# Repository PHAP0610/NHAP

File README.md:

# STM32F103

## Hardware BOARD V0.1

All file include and source in this: https://github.com/nguyentrungthao/STM32/tree/dev

### Module 7 segment with two ic 74595
1. Pin configuration.

<!-- cách ra 1 dòng để git hiểu là xuống hàng -->
<!-- :--- là căn trái :---: là căn giữa ---: là căn phải trong cột -->
| STM32 | 74595  | 
| :---: | :---: | 
| PA4 | SER |
| PA5 | OE |
| PA6 | RCLK |
| PA7 | SRCLK |

2. Code 

high 8-bit to select a 7-segment digit 
low 8-bit is code-7-segment 
code7segment is used in this board sequence:
<!--  có nhiều fotmat khác như c, cpp, js, html,...... -->
```c
/* this code only use for this version board */
const char code7seg[] = {0xD7, 0x14, 0xCD, 0x5D, 0x1E, 0x5B, 0xDB, 0x15, 0xDF, 0x5F};
```
### Module rotary encoder 
1. Pin configuration 

| STM32 | Rotary Encoder | description | 
| :---: | :---: | :--- |
| PA8 | channel A | pull up |
| PA9 | channel B | pull up |
| PA10 | buttuon | pull up |

2. Code

PA8 - PA9 is encoder mode of timer1 
```c
/* Enable TIM1 encoder mode */
/* USER CODE BEGIN 2 */
HAL_TIM_Encoder_Start_IT(&htim1, TIM_CHANNEL_ALL);
/* USER CODE END 2 */

/* Get encoder value */
encoderValue = __HAL_TIM_GetCounter(&htim1);
```

### AC voltage control
1. Pin configuration 

| STM32 | Module | description |
| :---: | :---: | :--- |
| PB0 | AC Detec| pull up |
| PB1 | Triac |  |

2. code 

PB0 should be an EXT pin 
``` c
/* proccess when interrupt */
void HAL_GPIO_EXTI_Callback(uint16_t GPIO_Pin){
	if(GPIO_Pin == ACDET_Pin){
		SETFLAG(FLAG_ACDET_TRIGGER, flag);
        // control angle to set triac base on time which is calculated by PID
		__HAL_TIM_SET_COUNTER(&htim4, (uint16_t)(triac.giaTriDieuKhien * 1000));
//		__HAL_TIM_SET_COUNTER(&htim4, 9000);
	}
}
```

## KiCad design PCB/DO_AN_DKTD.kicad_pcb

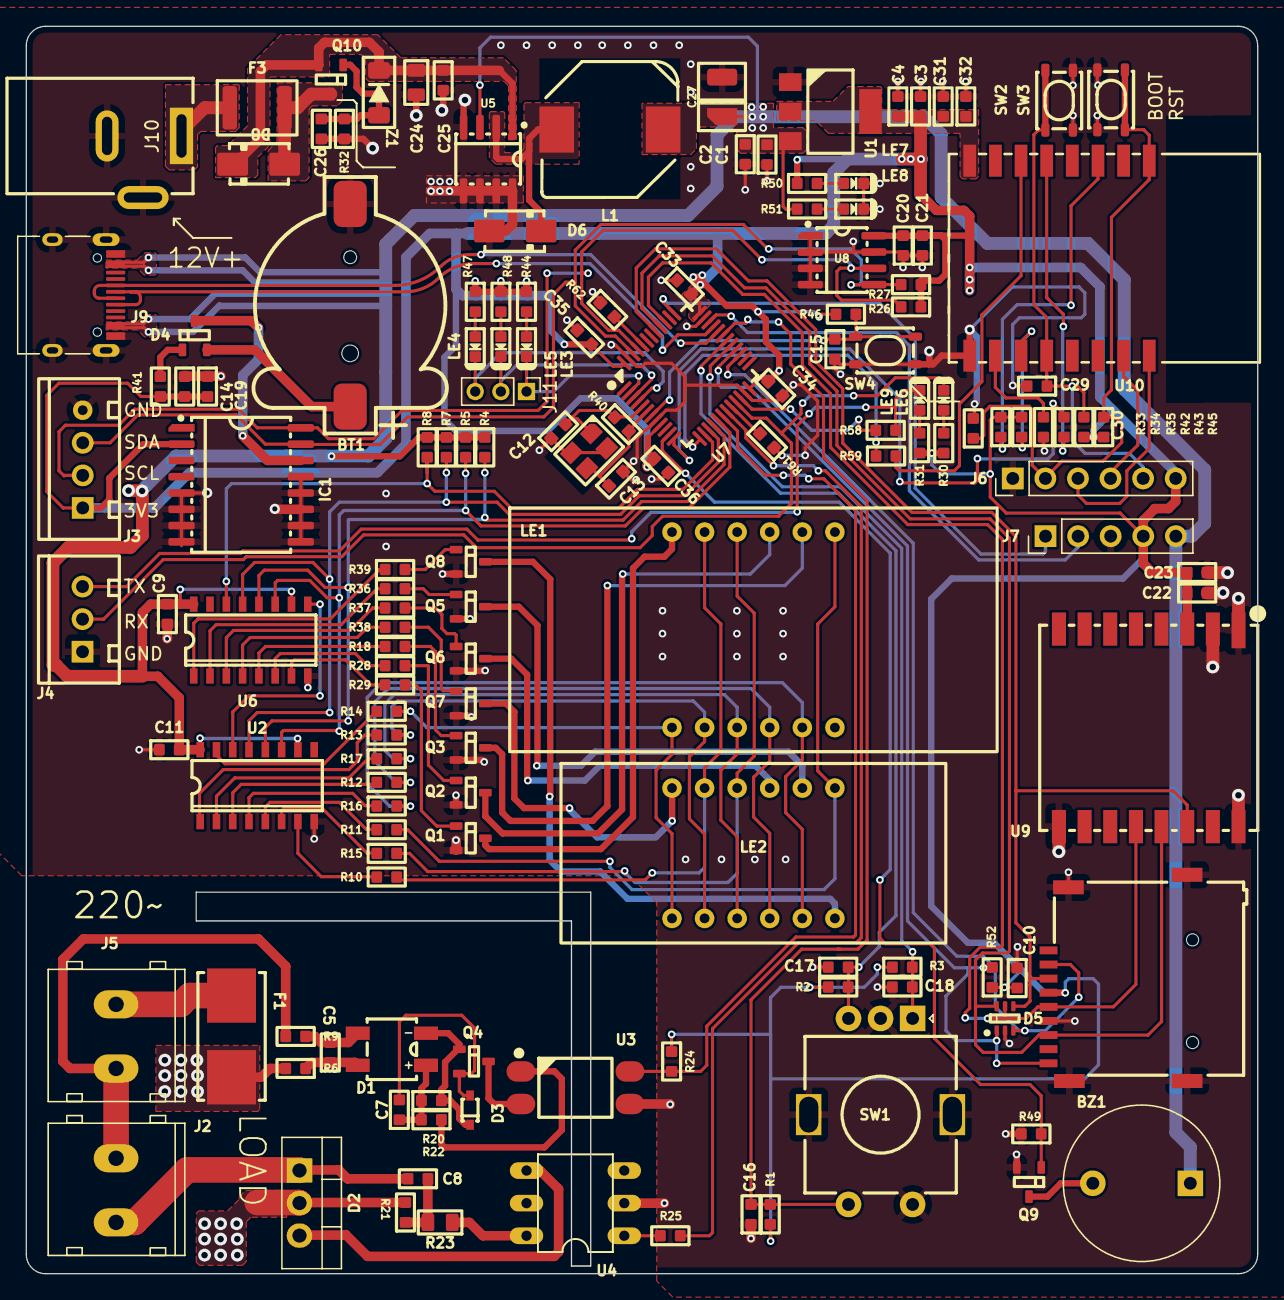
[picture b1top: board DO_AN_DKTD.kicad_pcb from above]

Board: 2 copper layers, 96.0 x 97.2 mm, 147 parts (0 on the bottom side), 115 nets.

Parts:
BT1: CR1220; BatteryHolder_CR1220
BZ1: Buzzer; Buzzer_12x9.5RM7.6
C1, C3, C15, C16, C17, C18, C22, C25, C29, C30, C31: 1uF; C_0603
C2, C4, C9, C10, C11, C19, C21, C23, C26, C32, C33, C34, C35, C36: 100nF; C_0603
C5: 10nF; C_0603
C7, C14, C20: 10uF; C_0603
C8: 50nF; C_0603
C12, C13: 22pF; C_0603
C24: 10uF; C_0805
C27: 10uF; CP_EIA-3528-15_AVX-H
D1: MB10F; DiodeBridge_MB10F-13AQ
D2: TRIAC; TO-220-3_Vertical
D3: 1N4148; D_SOD323
D4: BAT54C; SOT23-3
D5: SMF05C; TSSOP-6
D6, D8: SS54; D_SMA
F1: Fuse; Fuseholder_Littelfuse_Nano2_154x
F3: Fuse; Fuse_1812_4532Metric
IC1: RTC_DS3231M; SOIC-16W_7.5x10.3mm_P1.27mm
J2, J5: Conn_01x02; KF128-5.0-2P
J3: Conn_01x04; Conn_XH-P2.54mm-4P
J4: Conn_01x03; Conn_XH-P2.54mm-3P
J6: PinHeader_1x06_P2.54mm_Vertical
J7: Conn_01x05_Male; PinHeader_1x05_P2.54mm_Vertical
J9: USB_C_Receptacle; USB_C_Receptacle_XKB_U262-16XN-4BVC11
J10: Jack-DC; BarrelJack_Wuerth_6941xx301002
J11: Conn_01x03_Pin; PinHeader_1x03_P2.00mm_Vertical
J12: Micro_SD_Card_Det1; Socket_MicroSD-9P
L1: 68uH 2A; L_10.4x10.4_H4.8
LE1: 5631AS; 7Segment_4led_CC_38x19
LE2: 5631AS; 7Segment_4led_Cathode_30x14mm
LE3, LE4, LE5, LE6, LE7, LE8, LE9: Led; LED_0603
Q1, Q2, Q3, Q4, Q5, Q6, Q7, Q8: NPN; SOT23-3
Q9: N_Mosfet; SOT23-3
Q10: P_Mosfet; SOT23-3
R1, R2, R3, R4, R5, R7, R8, R26, R27, R52: 4k7; R_0603
R6, R9: 180k; R_0603
R10, R11, R12, R13, R14, R15, R16, R17, R22, R24, R30, R31, R41, R44, R47, R48, R50, R51: 1k; R_0603
R18, R28, R29, R36, R37, R38, R39: 2k; R_0603
R20: 22k; R_0603
R21: 470; R_0603
R23: 360; R_0805
R25: 360; R_0603
R32: 12k; R_0603
R33, R34, R35, R43, R45, R46: 10k; R_0603
R40, R49: 1M; R_0603
R42: 100; R_0603
R58, R59: 100R; R_0603
R61, R62: 10K; R_0603
SW1: RotaryEncoder_Switch; RotaryEncoder_Alps_EC11E-Switch_Vertical_H20mm
SW2, SW3, SW4: SW_Push; SW_SPST_PTS810
U1: AMS1117; SOT233
U2, U6: 74HC595; SOIC-16W_3.92x10.2mm
U3: PC817; OPTO_SOT254P975X400-4N
U4: MOC3020M; DIL06-E
U5: XL1509; SOIC-8_3.9x4.9mm_P1.27mm
U7: STM32F103C8Tx; LQFP-48_7x7mm_P0.5mm
U8: 24C32N; SOIC-8_3.9x4.9mm_P1.27mm
U9: Ai-Thinker-Ra-02; MODULE_RA-02_LORA
U10: ESP-07; ESP8266-07__ESP32-C3-12F
Y1: Crystal_GND24_Small; Crystal-SMD-4P-3.2x2.6mm-3225
Z1: D_Zener; D_MiniMELF

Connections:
+3V3: C3.2, C4.1, C10.2, C14.2, C19.2, C20.2, C21.2, C22.1, C23.1, C31.1, C32.1, C33.2, C34.2, C35.2, C36.2, IC1.2 (VCC), J3.1, J6.6, J7.4, J12.4 (VDD), R1.1, R2.1, R3.1, R24.1, R26.1, R27.1, R30.1, R31.1, R33.2, R34.2, R41.1, R43.1, R44.1, R45.1, R46.1, R47.1, R48.1, R50.1, R52.1, U1.2 (VO), U7.9 (VDDA), U7.24 (VDD), U7.36 (VDD), U7.48 (VDD), U8.8 (VCC), U9.3 (VDD), U10.8 (VCC)
+5V: BZ1.1 (-), C1.2, C2.1, C9.2, C11.2, C27.1, J7.5, J9.A4 (VBUS), J9.A9 (VBUS), J9.B4 (VBUS), J9.B9 (VBUS), L1.2, R4.1, R5.1, R7.1, R8.1, R51.1, U1.3 (VI), U2.10 (~SRCLR), U2.16 (VCC), U5.3 (FB), U6.10 (~SRCLR), U6.16 (VCC)
/74HC595_HEADER_OUTPUT/74HC595.OE: R7.2, U2.13 (~OE), U6.13 (~OE), U7.15 (PA5)
/74HC595_HEADER_OUTPUT/74HC595.RCLK: R4.2, U2.12 (RCLK), U6.12 (RCLK), U7.16 (PA6)
/74HC595_HEADER_OUTPUT/74HC595.SER: R8.2, U6.14 (SER), U7.14 (PA4)
/74HC595_HEADER_OUTPUT/74HC595.SRCLK: R5.2, U2.11 (SRCLK), U6.11 (SRCLK), U7.17 (PA7)
/74HC595_HEADER_OUTPUT/LE1: R29.1, U6.7 (QH)
/74HC595_HEADER_OUTPUT/LE2: R28.1, U6.6 (QG)
/74HC595_HEADER_OUTPUT/LE3: R18.1, U6.5 (QF)
/74HC595_HEADER_OUTPUT/LE4: R38.1, U6.4 (QE)
/74HC595_HEADER_OUTPUT/LE5: R37.1, U6.3 (QD)
/74HC595_HEADER_OUTPUT/LE6: R36.1, U6.2 (QC)
/74HC595_HEADER_OUTPUT/LE7: R39.1, U6.1 (QB)
/74HC595_HEADER_OUTPUT/LOG_RX: J4.2, LE6.2, U7.21 (PB10)
/74HC595_HEADER_OUTPUT/LOG_TX: J4.3, LE9.2, R58.1
/74HC595_HEADER_OUTPUT/SHT31.SCL: IC1.16 (SCL), J3.2, R26.2, U7.45 (PB8), U8.6 (SCL)
/74HC595_HEADER_OUTPUT/SHT31.SDA: IC1.15 (SDA), J3.3, R27.2, U7.46 (PB9), U8.5 (SDA)
/74HC595_HEADER_OUTPUT/a: LE1.11 (a), LE2.11 (a), R10.2
/74HC595_HEADER_OUTPUT/b: LE1.7 (b), LE2.7 (b), R11.2
/74HC595_HEADER_OUTPUT/c: LE1.4 (c), LE2.4 (c), R12.2
/74HC595_HEADER_OUTPUT/d: LE1.2 (d), LE2.2 (d), R13.2
/74HC595_HEADER_OUTPUT/dot: LE1.3 (DPX), LE2.3 (DPX), R17.2
/74HC595_HEADER_OUTPUT/e: LE1.1 (e), LE2.1 (e), R14.2
/74HC595_HEADER_OUTPUT/f: LE1.10 (f), LE2.10 (f), R15.2
/74HC595_HEADER_OUTPUT/g: LE1.5 (g), LE2.5 (g), R16.2
/BUZZER/Buzzer: Q9.1 (G), R49.1, U7.11 (PA1)
/ESP/BOOT: C29.1, J6.5, R43.2, SW3.2, U10.18 (GPIO0)
/ESP/RST: C30.1, J6.2, R45.2, SW2.2, U10.1 (~RST)
/ESP/RX: J6.4, U10.21 (GPIO3/RXD)
/ESP/RX_ESP32: R42.2, U7.12 (PA2)
/ESP/TX: J6.3, U10.22 (GPIO1/TXD)
/ESP/TX_ESP32: R59.2, U10.6 (GPIO12)
/LORA/LORA.MISO: D5.6, J12.7 (DAT0), U7.40 (PB4), U9.13 (MISO)
/LORA/LORA.MOSI: D5.4, J12.3 (CMD), U7.41 (PB5), U9.14 (MOSI)
/LORA/LORA.SCK: D5.5, J12.5 (CLK), U7.39 (PB3), U9.12 (SCK)
/MICRO_SD/SD.CS: D5.3, J12.2 (DAT3/CD), U7.27 (PB14)
/MICRO_SD/SD.DET: D5.1, J12.9 (DET), R52.2, U7.28 (PB15)
/POWER/B: D8.1, F3.2, Q10.3 (D)
/POWER/VIN: F3.1, J10.1
/POWER/VOUT: D6.2, L1.1, U5.2 (OUTPUT)
/RTC_DS3231/Vbat: BT1.1 (+), D4.2
/STM32/ACDET: R24.2, U3.4, U7.18 (PB0)
/STM32/Led_test1: J11.1, LE3.2, U7.2 (PC13)
/STM32/Led_test2: J11.2, LE5.2, U7.3 (PC14)
/STM32/Led_test3: J11.3, LE4.2, U7.4 (PC15)
/STM32/PD0: C12.2, R40.1, U7.5 (PD0), Y1.1
/STM32/PD1: C13.1, R40.2, U7.6 (PD1), Y1.3
/STM32/RST: C15.1, R46.2, SW4.2, U7.7 (NRST)
/STM32/ST.D+: J9.A6 (D+), J9.B6 (D+), U7.33 (PA12)
/STM32/ST.D-: J9.A7 (D-), J9.B7 (D-), U7.32 (PA11)
/STM32/ST.EnC_A: C18.2, R3.2, SW1.A, U7.29 (PA8)
/STM32/ST.EnC_B: C17.2, R2.2, SW1.B, U7.30 (PA9)
/STM32/ST.EnC_BT: C16.2, R1.2, SW1.S1, U7.31 (PA10)
/STM32/SWCLK: J7.1, U7.37 (PA14)
/STM32/SWDIO: J7.2, U7.34 (PA13)
/STM32/TRIAC: R25.1, U7.19 (PB1)
/TRIAC_ACDET/L: F1.2, J5.1
/TRIAC_ACDET/L_after: D2.2 (A2), F1.1, R6.2, R21.2
/TRIAC_ACDET/Load: C8.2, D2.1 (A1), J2.2
/TRIAC_ACDET/N: J2.1, J5.2, R9.2
GND: BT1.2 (-), C1.1, C2.2, C3.1, C4.2, C9.1, C10.1, C11.1, C12.1, C13.2, C14.1, C15.2, C16.1, C17.1, C18.1, C19.1, C20.1, C21.1, C22.2, C23.2, C24.2, C25.2, C26.2, C27.2, C29.2, C30.2, C31.2, C32.2, C33.1, C34.1, C35.1, C36.1, D5.2, D6.1, IC1.5 (GND), IC1.6 (GND), IC1.7 (GND), IC1.8 (GND), IC1.9 (GND), IC1.10 (GND), IC1.11 (GND), IC1.12 (GND), IC1.13 (GND), J3.4, J4.1, J6.1, J7.3, J9.A1 (GND), J9.A12 (GND), J9.B1 (GND), J9.B12 (GND), J9.S1 (SHIELD), J10.2, J12.6 (VSS), J12.10 (SHIELD), LE7.2, LE8.2, Q1.2 (E), Q2.2 (E), Q3.2 (E), Q5.2 (E), Q6.2 (E), Q7.2 (E), Q8.2 (E), Q9.2 (S), R32.2, R35.1, R49.2, R61.1, R62.1, SW1.C, SW1.MP (Shield), SW1.S2, SW2.1, SW3.1, SW4.1, U1.1 (GND), U2.8 (GND), U3.3, U4.2, U5.4 (ON/OFF), U5.5 (GND), U5.6 (GND), U5.7 (GND), U5.8 (GND), U6.8 (GND), U7.8 (VSSA), U7.23 (VSS), U7.35 (VSS), U7.47 (VSS), U8.1 (A0), U8.2 (A1), U8.3 (A2), U8.4 (GND), U8.7 (WP), U9.1 (GND), U9.2 (GND), U9.9 (GND), U9.16 (GND), U10.15 (GND), Y1.2, Y1.4
unnamed: D4.3, IC1.14 (VBAT)
unnamed: BZ1.2 (+), Q9.3 (D)
unnamed: C5.1, D1.4, R6.1
unnamed: C5.2, D1.2, R9.1
unnamed: C8.1, R21.1, R23.2
unnamed: C7.1, D1.1 (+), R20.1, R22.2
unnamed: D1.3 (-), D3.2, Q4.1 (B), R20.2
unnamed: D2.3 (G), U4.4
unnamed: D4.1, R41.2
unnamed: LE1.12 (CC1), Q1.3 (C)
unnamed: LE1.9 (CC2), Q2.3 (C)
unnamed: LE1.8 (CC3), Q3.3 (C)
unnamed: LE2.12 (CC1), Q7.3 (C)
unnamed: LE2.9 (CC2), Q6.3 (C)
unnamed: LE2.8 (CC3), Q5.3 (C)
unnamed: LE2.6 (CC4), Q8.3 (C)
unnamed: LE3.1, R44.2
unnamed: LE4.1, R47.2
unnamed: LE5.1, R48.2
unnamed: LE6.1, R30.2
unnamed: LE7.1, R50.2
unnamed: LE8.1, R51.2
unnamed: LE9.1, R31.2
unnamed: Q1.1 (B), R29.2
unnamed: Q2.1 (B), R28.2
unnamed: Q3.1 (B), R18.2
unnamed: Q4.3 (C), U3.2
unnamed: C7.2, D3.1, Q4.2 (E)
unnamed: Q5.1 (B), R36.2
unnamed: Q6.1 (B), R37.2
unnamed: Q7.1 (B), R38.2
unnamed: Q8.1 (B), R39.2
unnamed: C26.1, Q10.1 (G), R32.1, Z1.1
unnamed: R22.1, U3.1
unnamed: R23.1, U4.6
unnamed: R25.2, U4.1
unnamed: R14.1, U2.15 (QA)
unnamed: R13.1, U2.1 (QB)
unnamed: R17.1, U2.2 (QC)
unnamed: R12.1, U2.3 (QD)
unnamed: R16.1, U2.4 (QE)
unnamed: R11.1, U2.5 (QF)
unnamed: R15.1, U2.6 (QG)
unnamed: R10.1, U2.7 (QH)
unnamed: U2.14 (SER), U6.9 (QH')
unnamed: R62.2, U7.44 (BOOT0)
unnamed: R59.1, U7.13 (PA3)
unnamed: R61.2, U7.20 (PB2)
unnamed: R58.2, U7.22 (PB11)
unnamed: R33.1, U10.3 (EN)
unnamed: R34.1, U10.17 (GPIO2)
unnamed: R42.1, U10.5 (GPIO14)
unnamed: R35.2, U10.16 (GPIO15)
VDC: C24.1, C25.1, D8.2, Q10.2 (S), U5.1 (VIN), Z1.2

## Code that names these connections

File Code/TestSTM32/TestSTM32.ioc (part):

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Mcu.Name=STM32F103C(8-B)Tx
Mcu.Package=LQFP48
Mcu.UserName=STM32F103C8Tx
PA1.GPIOParameters=GPIO_Label
PA1.GPIO_Label=BUZZER
PA1.Signal=GPIO_Output
PA10.GPIOParameters=GPIO_PuPd,GPIO_Label,GPIO_ModeDefaultEXTI
PA10.GPIO_Label=EnBtn
PA10.GPIO_ModeDefaultEXTI=GPIO_MODE_IT_FALLING
PA10.GPIO_PuPd=GPIO_PULLUP
PA10.Signal=GPXTI10
PA13.Mode=Serial_Wire
PA13.Signal=SYS_JTMS-SWDIO
PA14.Mode=Serial_Wire
PA14.Signal=SYS_JTCK-SWCLK
PA15.GPIOParameters=GPIO_PuPd,GPIO_Label,GPIO_ModeDefaultOutputPP
PA15.GPIO_Label=LORA_CS
PA15.GPIO_ModeDefaultOutputPP=GPIO_MODE_OUTPUT_PP
PA15.GPIO_PuPd=GPIO_PULLUP
PA15.Signal=GPIO_Output
PA4.GPIOParameters=GPIO_Label
PA4.GPIO_Label=HC595_DS
PA4.Signal=GPIO_Output
PA5.GPIOParameters=GPIO_Label
PA5.GPIO_Label=HC595_OE
PA5.Signal=GPIO_Output
PA6.GPIOParameters=GPIO_Label
PA6.GPIO_Label=HC595_LATCH
PA6.Signal=GPIO_Output
PA7.GPIOParameters=GPIO_Label
PA7.GPIO_Label=HC595_SCLK
PA7.Signal=GPIO_Output
PA8.GPIOParameters=GPIO_Label
PA8.GPIO_Label=EnA
PA8.Signal=GPXTI8
PA9.GPIOParameters=GPIO_Label
PA9.GPIO_Label=EnB
PA9.Signal=GPIO_Input
PB0.GPIOParameters=GPIO_PuPd,GPIO_Label
PB0.GPIO_Label=ACDET
PB0.GPIO_PuPd=GPIO_PULLUP
PB0.Signal=GPXTI0
PB1.GPIOParameters=GPIO_Label
PB1.GPIO_Label=TRIAC
PB1.Signal=GPIO_Output
PB10.Mode=Asynchronous
PB10.Signal=USART3_TX
PB11.Mode=Asynchronous
PB11.Signal=USART3_RX
PB14.GPIOParameters=GPIO_PuPd,GPIO_Label
PB14.GPIO_Label=SD_CS
PB14.GPIO_PuPd=GPIO_PULLUP
PB14.Signal=GPIO_Output
PB15.GPIOParameters=GPIO_PuPd,GPIO_Label
PB15.GPIO_Label=SD_DET
PB15.GPIO_PuPd=GPIO_PULLUP
PB15.Signal=GPIO_Output
PB3.Mode=Full_Duplex_Master
PB3.Signal=SPI1_SCK
PB4.Mode=Full_Duplex_Master
PB4.Signal=SPI1_MISO
PB5.Mode=Full_Duplex_Master
PB5.Signal=SPI1_MOSI
PB6.GPIOParameters=GPIO_PuPd,GPIO_Label
PB6.GPIO_Label=LORA_INT
PB6.GPIO_PuPd=GPIO_PULLUP
PB6.Signal=GPIO_Output
PB7.GPIOParameters=GPIO_PuPd,GPIO_Label
PB7.GPIO_Label=LORA_RST
PB7.GPIO_PuPd=GPIO_PULLUP
PB7.Signal=GPIO_Output
PB8.Mode=I2C
PB8.Signal=I2C1_SCL
PB9.Mode=I2C
PB9.Signal=I2C1_SDA
PC13-TAMPER-RTC.GPIOParameters=GPIO_Label
PC13-TAMPER-RTC.GPIO_Label=LE4
PC13-TAMPER-RTC.Signal=GPIO_Output
PC14-OSC32_IN.GPIOParameters=GPIO_Label
PC14-OSC32_IN.GPIO_Label=LE5
PC14-OSC32_IN.Signal=GPIO_Output
PC15-OSC32_OUT.GPIOParameters=GPIO_Label
PC15-OSC32_OUT.GPIO_Label=LE3
PC15-OSC32_OUT.Signal=GPIO_Output
RCC.HSE_VALUE=25000000
RCC.SYSCLKFreq_VALUE=64000000
RCC.SYSCLKSource=RCC_SYSCLKSOURCE_PLLCLK
board=custom

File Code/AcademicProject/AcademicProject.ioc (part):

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Mcu.Name=STM32F103C(8-B)Tx
Mcu.Package=LQFP48
Mcu.UserName=STM32F103C8Tx
PA10.GPIOParameters=GPIO_Label
PA10.GPIO_Label=EnC_BT
PA10.Signal=GPXTI10
PA13.Mode=Serial_Wire
PA13.Signal=SYS_JTMS-SWDIO
PA14.Mode=Serial_Wire
PA14.Signal=SYS_JTCK-SWCLK
PA2.GPIOParameters=GPIO_Label
PA2.GPIO_Label=ESP_TX
PA2.Mode=Asynchronous
PA2.Signal=USART2_TX
PA3.GPIOParameters=GPIO_Label
PA3.GPIO_Label=ESP_RX
PA3.Mode=Asynchronous
PA3.Signal=USART2_RX
PA4.GPIOParameters=GPIO_Speed,GPIO_PuPd,GPIO_Label,GPIO_ModeDefaultOutputPP
PA4.GPIO_Label=SER
PA4.GPIO_ModeDefaultOutputPP=GPIO_MODE_OUTPUT_OD
PA4.GPIO_PuPd=GPIO_NOPULL
PA4.GPIO_Speed=GPIO_SPEED_FREQ_HIGH
PA4.Signal=GPIO_Output
PA5.GPIOParameters=GPIO_Speed,GPIO_PuPd,GPIO_Label,GPIO_ModeDefaultOutputPP
PA5.GPIO_Label=OE
PA5.GPIO_ModeDefaultOutputPP=GPIO_MODE_OUTPUT_OD
PA5.GPIO_PuPd=GPIO_NOPULL
PA5.GPIO_Speed=GPIO_SPEED_FREQ_HIGH
PA5.Signal=GPIO_Output
PA6.GPIOParameters=GPIO_Speed,GPIO_PuPd,GPIO_Label,GPIO_ModeDefaultOutputPP
PA6.GPIO_Label=RCLK
PA6.GPIO_ModeDefaultOutputPP=GPIO_MODE_OUTPUT_OD
PA6.GPIO_PuPd=GPIO_NOPULL
PA6.GPIO_Speed=GPIO_SPEED_FREQ_HIGH
PA6.Signal=GPIO_Output
PA7.GPIOParameters=GPIO_Speed,GPIO_PuPd,GPIO_Label,GPIO_ModeDefaultOutputPP
PA7.GPIO_Label=SRCLK
PA7.GPIO_ModeDefaultOutputPP=GPIO_MODE_OUTPUT_OD
PA7.GPIO_PuPd=GPIO_NOPULL
PA7.GPIO_Speed=GPIO_SPEED_FREQ_HIGH
PA7.Signal=GPIO_Output
PA8.Signal=S_TIM1_CH1
PA9.Signal=S_TIM1_CH2
PB0.GPIOParameters=GPIO_Label,GPIO_ModeDefaultEXTI
PB0.GPIO_Label=ACDET
PB0.GPIO_ModeDefaultEXTI=GPIO_MODE_IT_FALLING
PB0.Signal=GPXTI0
PB1.GPIOParameters=GPIO_Speed,GPIO_Label
PB1.GPIO_Label=TRIAC
PB1.GPIO_Speed=GPIO_SPEED_FREQ_HIGH
PB1.Signal=GPIO_Output
PB10.GPIOParameters=GPIO_Label
PB10.GPIO_Label=LOG_TX
PB10.Mode=Asynchronous
PB10.Signal=USART3_TX
PB11.GPIOParameters=GPIO_Label
PB11.GPIO_Label=LOG_RX
PB11.Mode=Asynchronous
PB11.Signal=USART3_RX
PB8.Mode=I2C
PB8.Signal=I2C1_SCL
PB9.Mode=I2C
PB9.Signal=I2C1_SDA
PC13-TAMPER-RTC.GPIOParameters=GPIO_Speed,PinState,GPIO_Label
PC13-TAMPER-RTC.GPIO_Label=LED1
PC13-TAMPER-RTC.GPIO_Speed=GPIO_SPEED_FREQ_HIGH
PC13-TAMPER-RTC.PinState=GPIO_PIN_SET
PC13-TAMPER-RTC.Signal=GPIO_Output
PC14-OSC32_IN.GPIOParameters=GPIO_Speed,PinState,GPIO_Label
PC14-OSC32_IN.GPIO_Label=LED2
PC14-OSC32_IN.GPIO_Speed=GPIO_SPEED_FREQ_HIGH
PC14-OSC32_IN.PinState=GPIO_PIN_SET
PC14-OSC32_IN.Signal=GPIO_Output
PC15-OSC32_OUT.GPIOParameters=GPIO_Speed,PinState,GPIO_Label
PC15-OSC32_OUT.GPIO_Label=LED3
PC15-OSC32_OUT.GPIO_Speed=GPIO_SPEED_FREQ_HIGH
PC15-OSC32_OUT.PinState=GPIO_PIN_SET
PC15-OSC32_OUT.Signal=GPIO_Output
PD0-OSC_IN.Mode=HSE-External-Oscillator
PD0-OSC_IN.Signal=RCC_OSC_IN
PD1-OSC_OUT.Mode=HSE-External-Oscillator
PD1-OSC_OUT.Signal=RCC_OSC_OUT
board=custom

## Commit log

2023-05-15 init git, .gitignore, README.md and copy file from project 1
2023-05-15 update README discription board
2023-05-17 init new project to clear code, update link LIB STM32
2023-07-05 make a file
2023-07-05 remove config USB
2023-07-05 add Buzzer code
2023-07-05 7seg Test all output OK
2023-07-05 7 seg Test digit output OK
2023-07-07 Run timer with 10ms interrupt
2023-07-07 Test code 7seg 0-9
2023-07-07 count up from 0 to 999
2023-07-09 Test Encoder OK
2023-07-10 raw placement
2023-07-11 test
2023-07-11 upgrade code
2023-07-11 layout pcb p2
2023-07-12 read encoder by timer
2023-07-13 7seg with Timer
2023-07-13 encoder ngat ngoai
2023-07-13 Update PCB
2023-07-13 Encoder with interrupt
2023-07-13 Adding UART log
2023-07-13 Add UART
2023-07-14 Test board A Thao
2023-07-14 Read encoder with flag
2023-07-15 Mini layout p3
2023-07-18 ECD without capacity
2023-07-19 Update code
2023-07-20 clock issue
2023-07-20 Encoder and Button with Interrupt
2023-07-22 Update code day 22
2023-07-25 update 25/7
2023-07-26 update 26/7
2023-07-27 Update some footprints name
2023-07-29 Receive error
2023-07-30 UART update

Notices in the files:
parts and their libraries:
Copyright 2021 Accelerated Designs. All rights reserved.
